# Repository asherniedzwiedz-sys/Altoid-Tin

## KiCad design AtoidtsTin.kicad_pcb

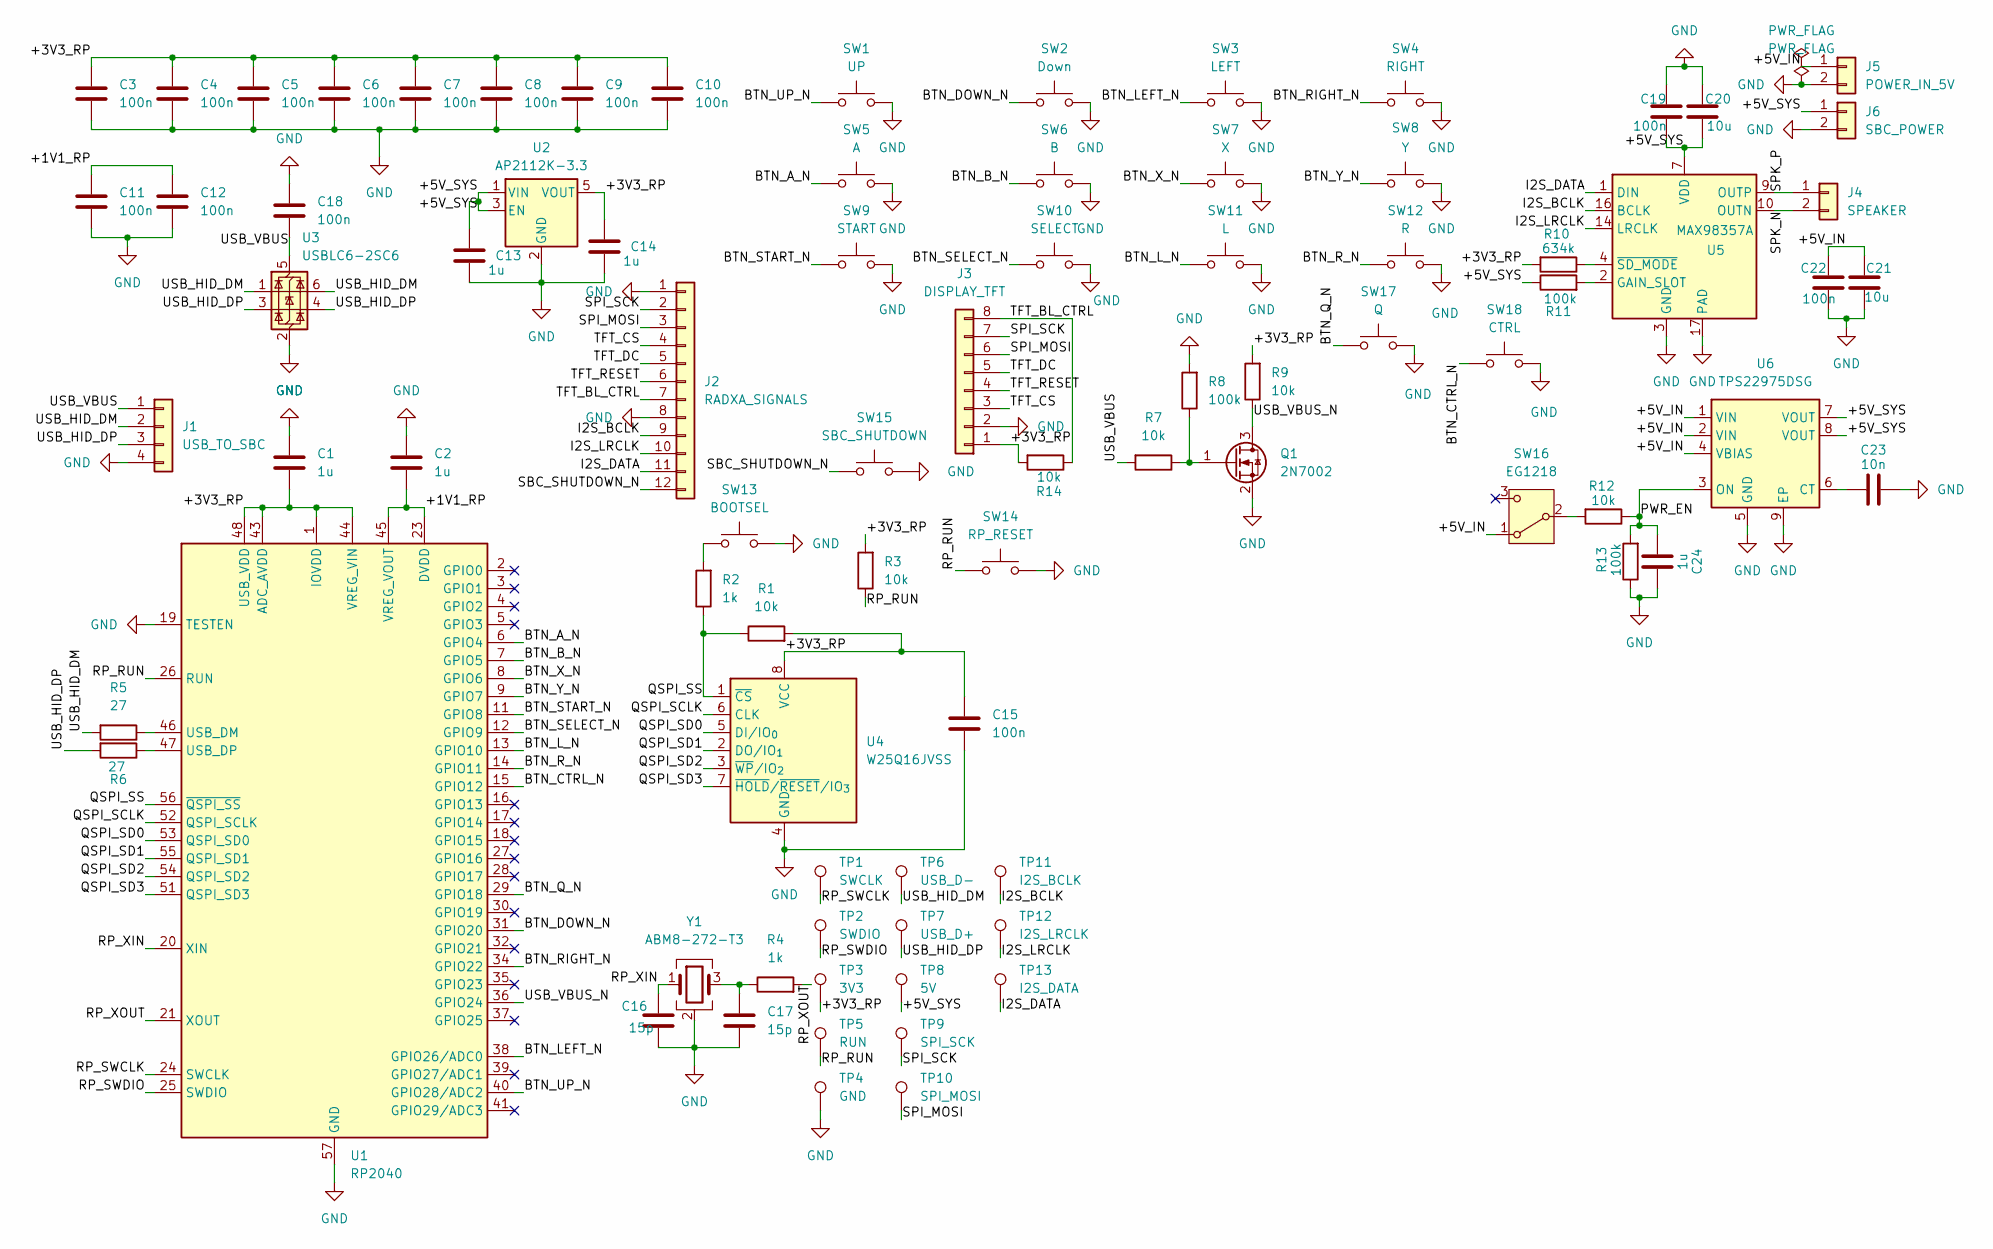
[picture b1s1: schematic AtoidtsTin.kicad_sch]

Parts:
C1, C2, C13, C14, C24: 1u; C_0603_1608Metric
C3, C4, C5, C6, C7, C8, C9, C10, C11, C15, C18, C19, C22: 100n; C_0603_1608Metric
C12: 100n; C_0402_1005Metric
C16, C17: 15p; C_0603_1608Metric
C20, C21: 10u; C_0805_2012Metric
C23: 10n; C_0603_1608Metric
J1: USB_TO_SBC; PinHeader_1x04_P2.54mm_Vertical
J2: RADXA_SIGNALS; PinHeader_1x12_P2.54mm_Vertical
J3: DISPLAY_TFT; PinHeader_1x08_P2.54mm_Vertical
J4: SPEAKER; PinHeader_1x02_P2.54mm_Vertical
J5: POWER_IN_5V; PinHeader_1x02_P2.54mm_Vertical
J6: SBC_POWER; PinHeader_1x02_P2.54mm_Vertical
Q1: 2N7002; SOT-23
R1, R3, R7, R9, R12, R14: 10k; R_0603_1608Metric
R2, R4: 1k; R_0603_1608Metric
R5, R6: 27; R_0603_1608Metric
R8, R11, R13: 100k; R_0603_1608Metric
R10: 634k; R_0603_1608Metric
SW1: UP; SW_PUSH_6mm
SW2: Down; SW_PUSH_6mm
SW3: LEFT; SW_PUSH_6mm
SW4: RIGHT; SW_PUSH_6mm
SW5: A; SW_PUSH_6mm
SW6: B; SW_PUSH_6mm
SW7: X; SW_PUSH_6mm
SW8: Y; SW_PUSH_6mm
SW9: START; SW_PUSH_6mm
SW10: SELECT; SW_PUSH_6mm
SW11: L; SW_PUSH_6mm
SW12: R; SW_PUSH_6mm
SW13: BOOTSEL; SW_PUSH_6mm
SW14: RP_RESET; SW_PUSH_6mm
SW15: SBC_SHUTDOWN; SW_PUSH_6mm
SW16: EG1218; Switch_Slide_11.6x4mm_EG1218
SW17: Q; SW_PUSH_6mm
SW18: CTRL; SW_PUSH_6mm
TP1: SWCLK; TestPoint_Pad_D1.5mm
TP2: SWDIO; TestPoint_Pad_D1.5mm
TP3: 3V3; TestPoint_Pad_D1.5mm
TP4: GND; TestPoint_Pad_D1.5mm
TP5: RUN; TestPoint_Pad_D1.5mm
TP6: USB_D-; TestPoint_Pad_D1.0mm
TP7: USB_D+; TestPoint_Pad_D1.0mm
TP8: 5V; TestPoint_Pad_D1.5mm
TP9: SPI_SCK; TestPoint_Pad_D1.5mm
TP10: SPI_MOSI; TestPoint_Pad_D1.5mm
TP11: I2S_BCLK; TestPoint_Pad_D1.5mm
TP12: I2S_LRCLK; TestPoint_Pad_D1.5mm
TP13: I2S_DATA; TestPoint_Pad_D1.5mm
U1: RP2040; QFN-56-1EP_7x7mm_P0.4mm_EP3.2x3.2mm
U2: AP2112K-3.3; SOT-23-5
U3: USBLC6-2SC6; SOT-23-6
U4: W25Q16JVSS; SOIC-8_5.3x5.3mm_P1.27mm
U5: MAX98357A; TQFN-16-1EP_3x3mm_P0.5mm_EP1.23x1.23mm
U6: TPS22975DSG; DFN-8-1EP_2x2mm_P0.5mm_EP0.9x1.6mm; MPN TPS22975DSGR
Y1: ABM8-272-T3; Crystal_SMD_3225-4Pin_3.2x2.5mm

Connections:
/+1V1_RP: C2.1, C11.1, C12.1, U1.23 (DVDD), U1.45 (VREG_VOUT), U1.50 (DVDD)
/+3V3_RP: C1.1, C3.1, C4.1, C5.1, C6.1, C7.1, C8.1, C9.1, C10.1, C14.1, C15.1, J3.1, R1.2, R3.2, R9.2, R10.2, R14.2, TP3.1 (1_1), U1.1 (IOVDD), U1.10 (IOVDD), U1.22 (IOVDD), U1.33 (IOVDD), U1.42 (IOVDD), U1.43 (ADC_AVDD), U1.44 (VREG_VIN), U1.48 (USB_VDD), U1.49 (IOVDD), U2.5 (VOUT), U4.8 (VCC)
/+5V_IN: C21.1, C22.2, J5.1, SW16.1 (A), U6.1 (VIN), U6.2 (VIN), U6.4 (VBIAS)
/+5V_SYS: C13.1, C19.1, C20.1, J6.1, R11.1, TP8.1 (1_1), U2.1 (VIN), U2.3 (EN), U5.7 (VDD), U5.8 (VDD), U6.7 (VOUT), U6.8 (VOUT)
/BTN_A_N: SW5.1, U1.6 (GPIO4)
/BTN_B_N: SW6.1, U1.7 (GPIO5)
/BTN_CTRL_N: SW18.1, U1.15 (GPIO12)
/BTN_DOWN_N: SW2.1, U1.31 (GPIO20)
/BTN_LEFT_N: SW3.1, U1.38 (GPIO26/ADC0)
/BTN_L_N: SW11.1, U1.13 (GPIO10)
/BTN_Q_N: SW17.1, U1.29 (GPIO18)
/BTN_RIGHT_N: SW4.1, U1.34 (GPIO22)
/BTN_R_N: SW12.1, U1.14 (GPIO11)
/BTN_SELECT_N: SW10.1, U1.12 (GPIO9)
/BTN_START_N: SW9.1, U1.11 (GPIO8)
/BTN_UP_N: SW1.1, U1.40 (GPIO28/ADC2)
/BTN_X_N: SW7.1, U1.8 (GPIO6)
/BTN_Y_N: SW8.1, U1.9 (GPIO7)
/I2S_BCLK: J2.9, TP11.1 (1_1), U5.16 (BCLK)
/I2S_DATA: J2.11, TP13.1 (1_1), U5.1 (DIN)
/I2S_LRCLK: J2.10, TP12.1 (1_1), U5.14 (LRCLK)
/PWR_EN: C24.2, R12.1, R13.2, U6.3 (ON)
/QSPI_SCLK: U1.52 (QSPI_SCLK), U4.6 (CLK)
/QSPI_SD0: U1.53 (QSPI_SD0), U4.5 (DI/IO_{0})
/QSPI_SD1: U1.55 (QSPI_SD1), U4.2 (DO/IO_{1})
/QSPI_SD2: U1.54 (QSPI_SD2), U4.3 (~WP/IO_{2})
/QSPI_SD3: U1.51 (QSPI_SD3), U4.7 (~HOLD/~RESET/IO_{3})
/QSPI_SS: R1.1, R2.1, U1.56 (~QSPI_SS), U4.1 (~CS)
/RP_RUN: R3.1, SW14.1, TP5.1 (1_1), U1.26 (RUN)
/RP_SWCLK: TP1.1 (1_1), U1.24 (SWCLK)
/RP_SWDIO: TP2.1 (1_1), U1.25 (SWDIO)
/RP_XIN: C16.1, U1.20 (XIN), Y1.1
/RP_XOUT: R4.2, U1.21 (XOUT)
/SBC_SHUTDOWN_N: J2.12, SW15.1
/SPI_MOSI: J2.3, J3.6, TP10.1 (1_1)
/SPI_SCK: J2.2, J3.7, TP9.1 (1_1)
/SPK_N: J4.2, U5.10 (OUTN)
/SPK_P: J4.1, U5.9 (OUTP)
/TFT_BL_CTRL: J2.7, J3.8, R14.1
/TFT_CS: J2.4, J3.3
/TFT_DC: J2.5, J3.5
/TFT_RESET: J2.6, J3.4
/USB_HID_DM: J1.2, R5.2, TP6.1 (1_1), U3.1 (I/O1), U3.6 (I/O1)
/USB_HID_DP: J1.3, R6.2, TP7.1 (1_1), U3.3 (I/O2), U3.4 (I/O2)
/USB_VBUS: C18.2, J1.1, R7.2, U3.5 (VBUS)
/USB_VBUS_N: Q1.3 (D), R9.1, U1.36 (GPIO24)
GND: C1.2, C2.2, C3.2, C4.2, C5.2, C6.2, C7.2, C8.2, C9.2, C10.2, C11.2, C12.2, C13.2, C14.2, C15.2, C16.2, C17.2, C18.1, C19.2, C20.2, C21.2, C22.1, C23.1, C24.1, J1.4, J2.1, J2.8, J3.2, J5.2, J6.2, Q1.2 (S), R8.2, R13.1, SW1.2, SW2.2, SW3.2, SW4.2, SW5.2, SW6.2, SW7.2, SW8.2, SW9.2, SW10.2, SW11.2, SW12.2, SW13.2, SW14.2, SW15.2, SW17.2, SW18.2, TP4.1 (1_1), U1.19 (TESTEN), U1.57 (GND), U2.2 (GND), U3.2 (GND), U4.4 (GND), U5.3 (GND), U5.11 (GND), U5.15 (GND), U5.17 (PAD), U6.5 (GND), U6.9 (EP), Y1.2 (G), Y1.4 (G)
unnamed: C17.1, R4.1, Y1.3
unnamed: Q1.1 (G), R7.1, R8.1
unnamed: R2.2, SW13.1
unnamed: R12.2, SW16.2 (B)
unnamed: R5.1, U1.46 (USB_DM)
unnamed: R6.1, U1.47 (USB_DP)
unnamed: R11.2, U5.2 (GAIN_SLOT)
unnamed: R10.1, U5.4 (~SD_MODE)
unnamed: C23.2, U6.6 (CT)

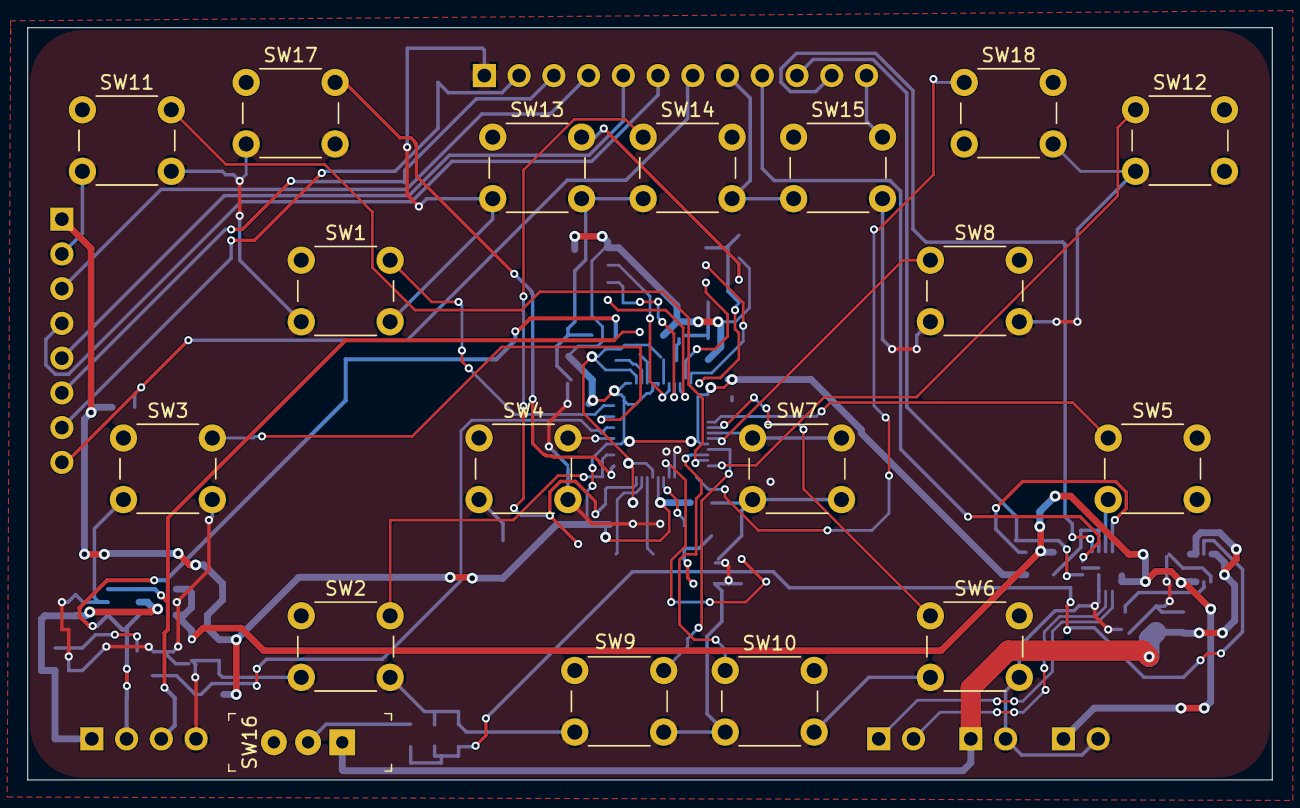
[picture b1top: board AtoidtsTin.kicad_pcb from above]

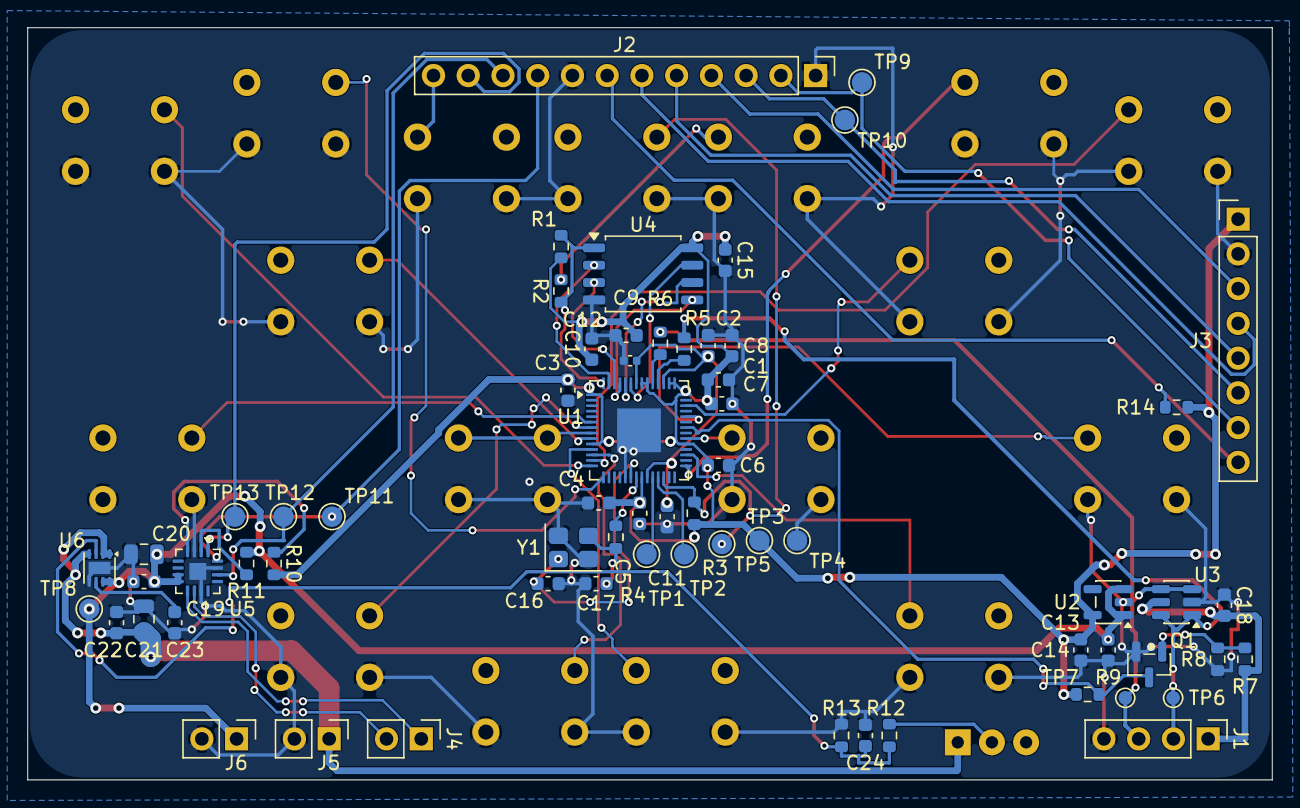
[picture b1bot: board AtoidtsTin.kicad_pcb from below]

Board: 2 copper layers, 91.0 x 55.0 mm, 83 parts (65 on the bottom side), 56 nets.
